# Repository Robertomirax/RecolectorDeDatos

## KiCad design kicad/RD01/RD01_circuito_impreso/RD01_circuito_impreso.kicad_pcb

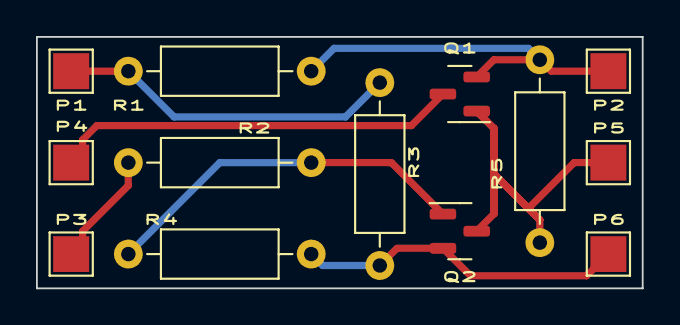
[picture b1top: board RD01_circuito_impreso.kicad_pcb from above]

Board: 2 copper layers, 33.7 x 14.0 mm, 13 parts (0 on the bottom side), 7 nets.

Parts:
P1: esp 35; TestPoint_Pad_2.0x2.0mm
P2: +Bat; TestPoint_Pad_2.0x2.0mm
P3: esp 26; TestPoint_Pad_2.0x2.0mm
P4: +Vcc; TestPoint_Pad_2.0x2.0mm
P5: bot encend; TestPoint_Pad_2.0x2.0mm
P6: GND; TestPoint_Pad_2.0x2.0mm
Q1: AO3401; SOT-23
Q2: AO3400; SOT-23
R1: 51K; R_Axial_DIN0207_L6.3mm_D2.5mm_P10.16mm_Horizontal
R2: 470; R_Axial_DIN0207_L6.3mm_D2.5mm_P10.16mm_Horizontal
R3: 68K; R_Axial_DIN0207_L6.3mm_D2.5mm_P10.16mm_Horizontal
R4, R5: 10K; R_Axial_DIN0207_L6.3mm_D2.5mm_P10.16mm_Horizontal

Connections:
Earth: P6.1, Q2.2 (S), R3.2, R4.2
unnamed: P1.1, R1.1, R3.1
unnamed: P3.1, R2.1
unnamed: P5.1, Q1.1 (G), Q2.3 (D), R5.1
unnamed: P4.1, Q1.3 (D)
unnamed: P2.1, Q1.2 (S), R1.2, R5.2
unnamed: Q2.1 (G), R2.2, R4.1

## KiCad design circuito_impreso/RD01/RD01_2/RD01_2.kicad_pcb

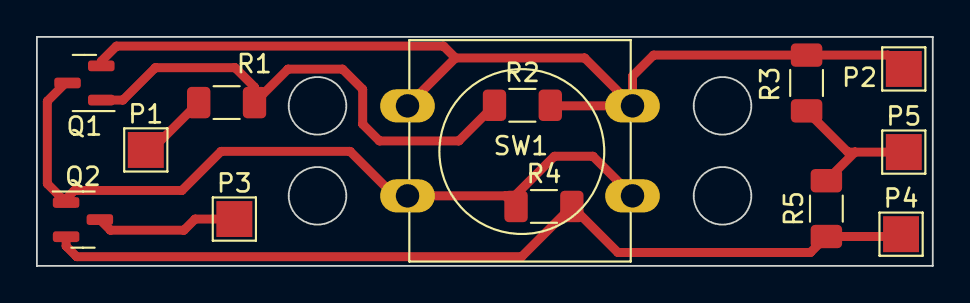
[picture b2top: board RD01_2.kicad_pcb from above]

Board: 2 copper layers, 49.8 x 12.7 mm, 13 parts (0 on the bottom side), 7 nets.

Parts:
P1: esp 26; TestPoint_Pad_2.0x2.0mm
P2: GND; TestPoint_Pad_2.0x2.0mm
P3: +Vcc; TestPoint_Pad_2.0x2.0mm
P4: +Bat; TestPoint_Pad_2.0x2.0mm
P5: esp 35; TestPoint_Pad_2.0x2.0mm
Q1: PN2222Asmd; SOT-23
Q2: DMG2305UX-7; SOT-23
R1: 470; R_1206_3216Metric_Pad1.30x1.75mm_HandSolder
R2, R4: 10K; R_1206_3216Metric_Pad1.30x1.75mm_HandSolder
R3: 68K; R_1206_3216Metric_Pad1.30x1.75mm_HandSolder
R5: 51K; R_1206_3216Metric_Pad1.30x1.75mm_HandSolder
SW1: encendido; SW_PUSH-12mm

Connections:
unnamed: P1.1, R1.1
unnamed: P2.1, Q1.2 (E), R2.2, R3.1, SW1.1
unnamed: P3.1, Q2.3 (D)
unnamed: P4.1, Q2.2 (S), R4.2, R5.1
unnamed: P5.1, R3.2, R5.2
unnamed: Q1.3 (C), Q2.1 (G), R4.1, SW1.2
unnamed: Q1.1 (B), R1.2, R2.1
